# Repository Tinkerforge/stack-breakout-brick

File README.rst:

Stack Breakout Brick
====================

**This Brick is currently in development.**

This repository contains the hardware design files.

Repository Content
------------------

hardware/:
 * Contains KiCad project files and additionally schematics as PDF

Hardware
--------

The hardware is designed with the open source EDA Suite KiCad
(http://www.kicad.org). Before you are able to open the files,
you have to install the Tinkerforge kicad-libraries
(https://github.com/Tinkerforge/kicad-libraries). You can either clone
them directly in hardware/ or clone them in a separate folder and
symlink them into hardware/
(ln -s kicad_path/kicad-libraries project_path/hardware). After that you
can open the .pro file in hardware/ with KiCad and from there view and
modify the schematics and the PCB layout.

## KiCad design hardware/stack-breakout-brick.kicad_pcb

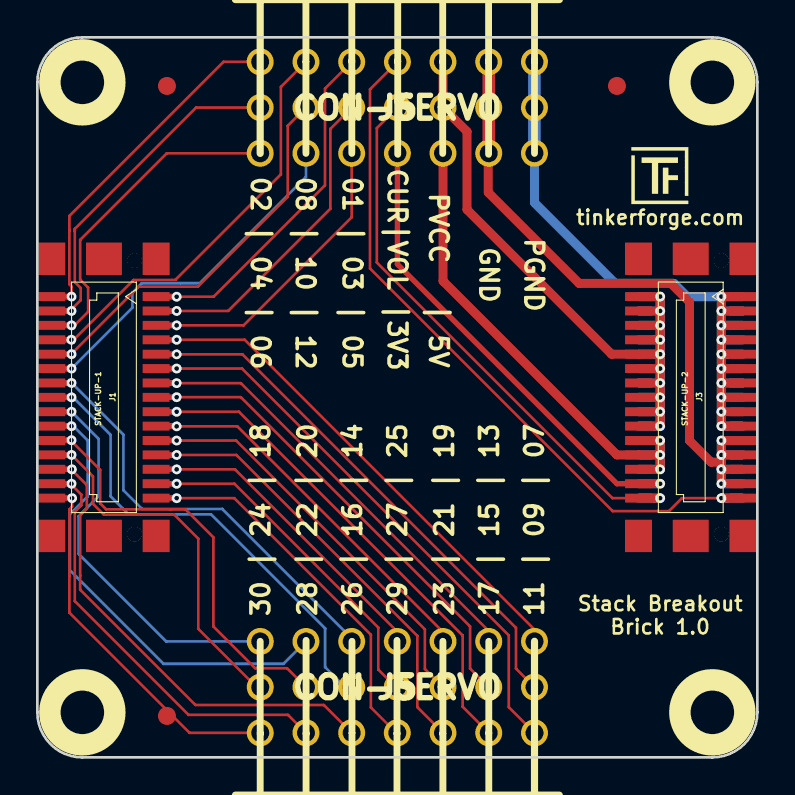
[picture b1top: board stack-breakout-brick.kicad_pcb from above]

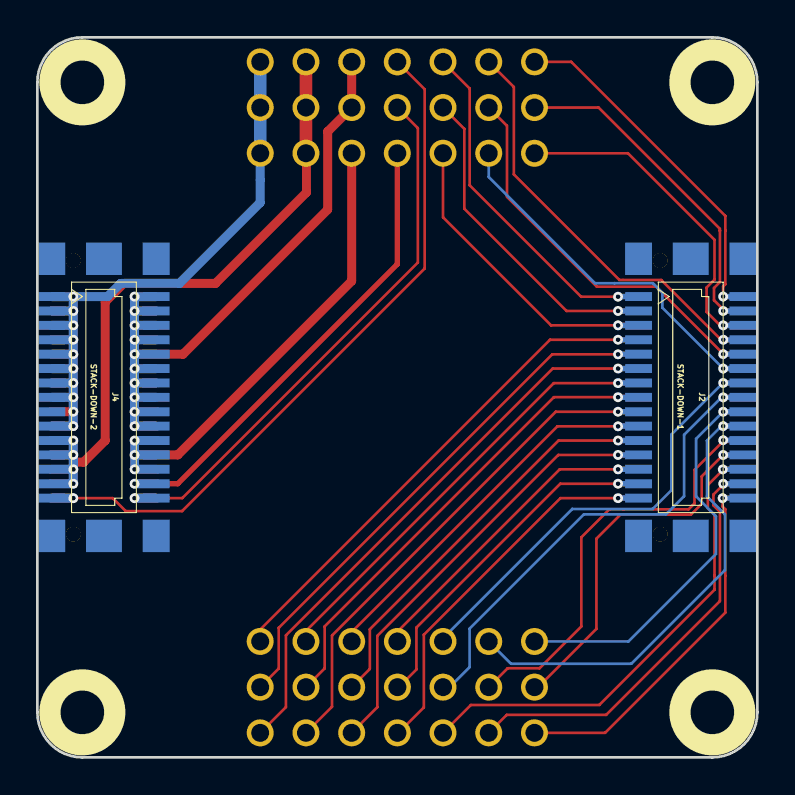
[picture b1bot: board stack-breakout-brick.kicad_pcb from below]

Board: 2 copper layers, 40.0 x 40.0 mm, 13 parts (2 on the bottom side), 37 nets.

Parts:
Fiducial_Mark: VAL**; Fiducial_Mark
Fiducial_Mark#2, Fiducial_Mark#3: VAL**; Fiducial_Mark
J1: STACK-UP-1; BTB08-ACS-TOP
J2: STACK-DOWN-1; BTB08-ACS-BTM
J3: STACK-UP-2; BTB08-ACS-TOP
J4: STACK-DOWN-2; BTB08-ACS-BTM
J5, J6: CON-SERVO; CON-Servo
U1, U2, U3, U4: DRILL; DRILL_NP

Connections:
3V3: J3.28, J4.28, J6.D3
5V: J3.22, J3.24, J3.26, J4.22, J4.24, J4.26, J6.C3
CURRENT: J3.29, J4.29, J6.D1
DETECT/TMS: J1.9, J2.9, J5.G2
EX-0-GP00: J1.19, J2.19, J5.E3
EX-0-GP01: J1.21, J2.21, J5.E2
EX-0-GP02: J1.23, J2.23, J5.E1
EX-1-GP00: J1.25, J2.25, J5.D3
EX-1-GP01: J1.27, J2.27, J5.D2
EX-1-GP02: J1.29, J2.29, J5.D1
EX-SEL-00: J1.22, J2.22, J5.B2
EX-SEL-01: J1.24, J2.24, J5.A2
EX-SER2-RTS: J1.30, J2.30, J5.A1
EX-SER2-RXD: J1.26, J2.26, J5.C1
EX-SER2-TXD: J1.28, J2.28, J5.B1
EX-SPI-MISO: J1.13, J2.13, J5.F3
EX-SPI-MOSI: J1.15, J2.15, J5.F2
EX-SPI-SCLK: J1.17, J2.17, J5.F1
GND: J1.EP, J2.EP, J3.21, J3.23, J3.25, J3.27, J3.EP, J4.21, J4.23, J4.25, J4.27, J4.EP, J6.B1, J6.B2, J6.B3
I2C-SCL: J1.4, J2.4, J6.G2
I2C-SDA: J1.2, J2.2, J6.G1
RESET: J1.7, J2.7, J5.G3
SEL-00: J1.6, J2.6, J6.G3
SEL-01: J1.8, J2.8, J6.F1
SEL-02: J1.10, J2.10, J6.F2
SEL-03: J1.12, J2.12, J6.F3
SEL-04: J1.14, J2.14, J5.C3
SEL-05: J1.16, J2.16, J5.C2
SEL-06: J1.18, J2.18, J5.A3
SEL-07: J1.20, J2.20, J5.B3
SPI-MISO: J1.1, J2.1, J6.E1
SPI-MOSI: J1.3, J2.3, J6.E2
SPI-SCLK: J1.5, J2.5, J6.E3
STACK-PGND: J3.1, J3.3, J3.5, J3.7, J3.9, J3.11, J3.13, J3.15, J3.17, J3.19, J4.1, J4.3, J4.5, J4.7, J4.9, J4.11, J4.13, J4.15, J4.17, J4.19, J6.A1, J6.A2, J6.A3
STACK-PVCC: J3.2, J3.4, J3.6, J3.8, J3.10, J3.12, J3.14, J3.16, J3.18, J3.20, J4.2, J4.4, J4.6, J4.8, J4.10, J4.12, J4.14, J4.16, J4.18, J4.20, J6.C1, J6.C2
SYNC/GP/TCK: J1.11, J2.11, J5.G1
VOLTAGE: J3.30, J4.30, J6.D2

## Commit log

2017-02-27 Add readme
2017-02-28 Initial check in
2017-03-01 Add schematic
2017-03-01 Add PCB layout
2017-03-01 Add pin labeling
2017-03-01 Add product name labeling
2017-03-02 Fix labeling and routing
2017-03-02 Fix fiducial marks
2017-03-02 Optical adjustments
2017-03-02 Add PDF schematic
2018-02-20 Add .gitignore
2018-02-20 Cleanup KiCad libraries config
    Ensure LibDir=kicad-libraries and LibName1=tinkerforge.
    Remove special library.
2021-10-25 Update KiCad link
    https://www.kicad.org/blog/2021/10/Avoid-links-to-former-kicad-domain/

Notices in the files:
hardware/stack-breakout-brick.kicad_pcb:
Licensed under CERN OHL v.1.1
Copyright (©) 2017, L.lauer
